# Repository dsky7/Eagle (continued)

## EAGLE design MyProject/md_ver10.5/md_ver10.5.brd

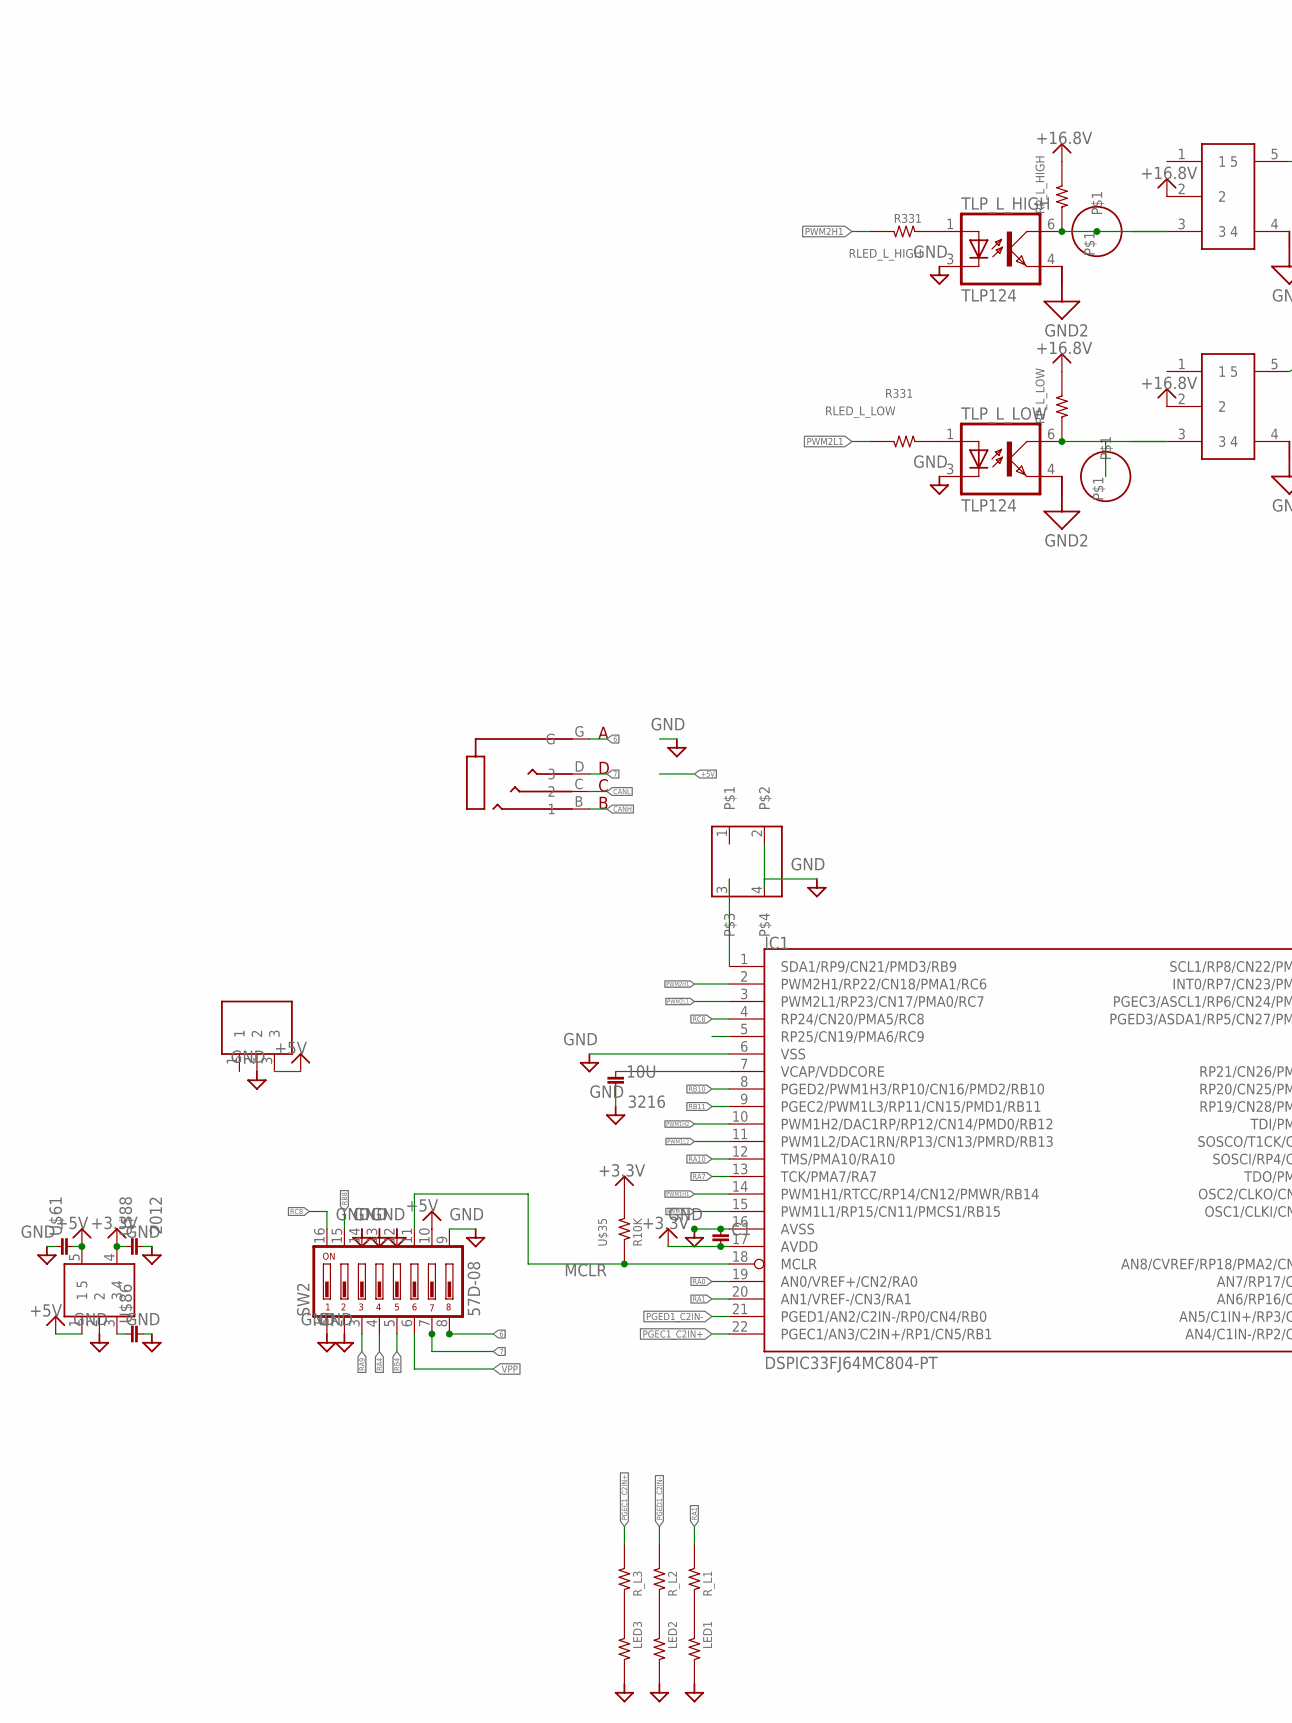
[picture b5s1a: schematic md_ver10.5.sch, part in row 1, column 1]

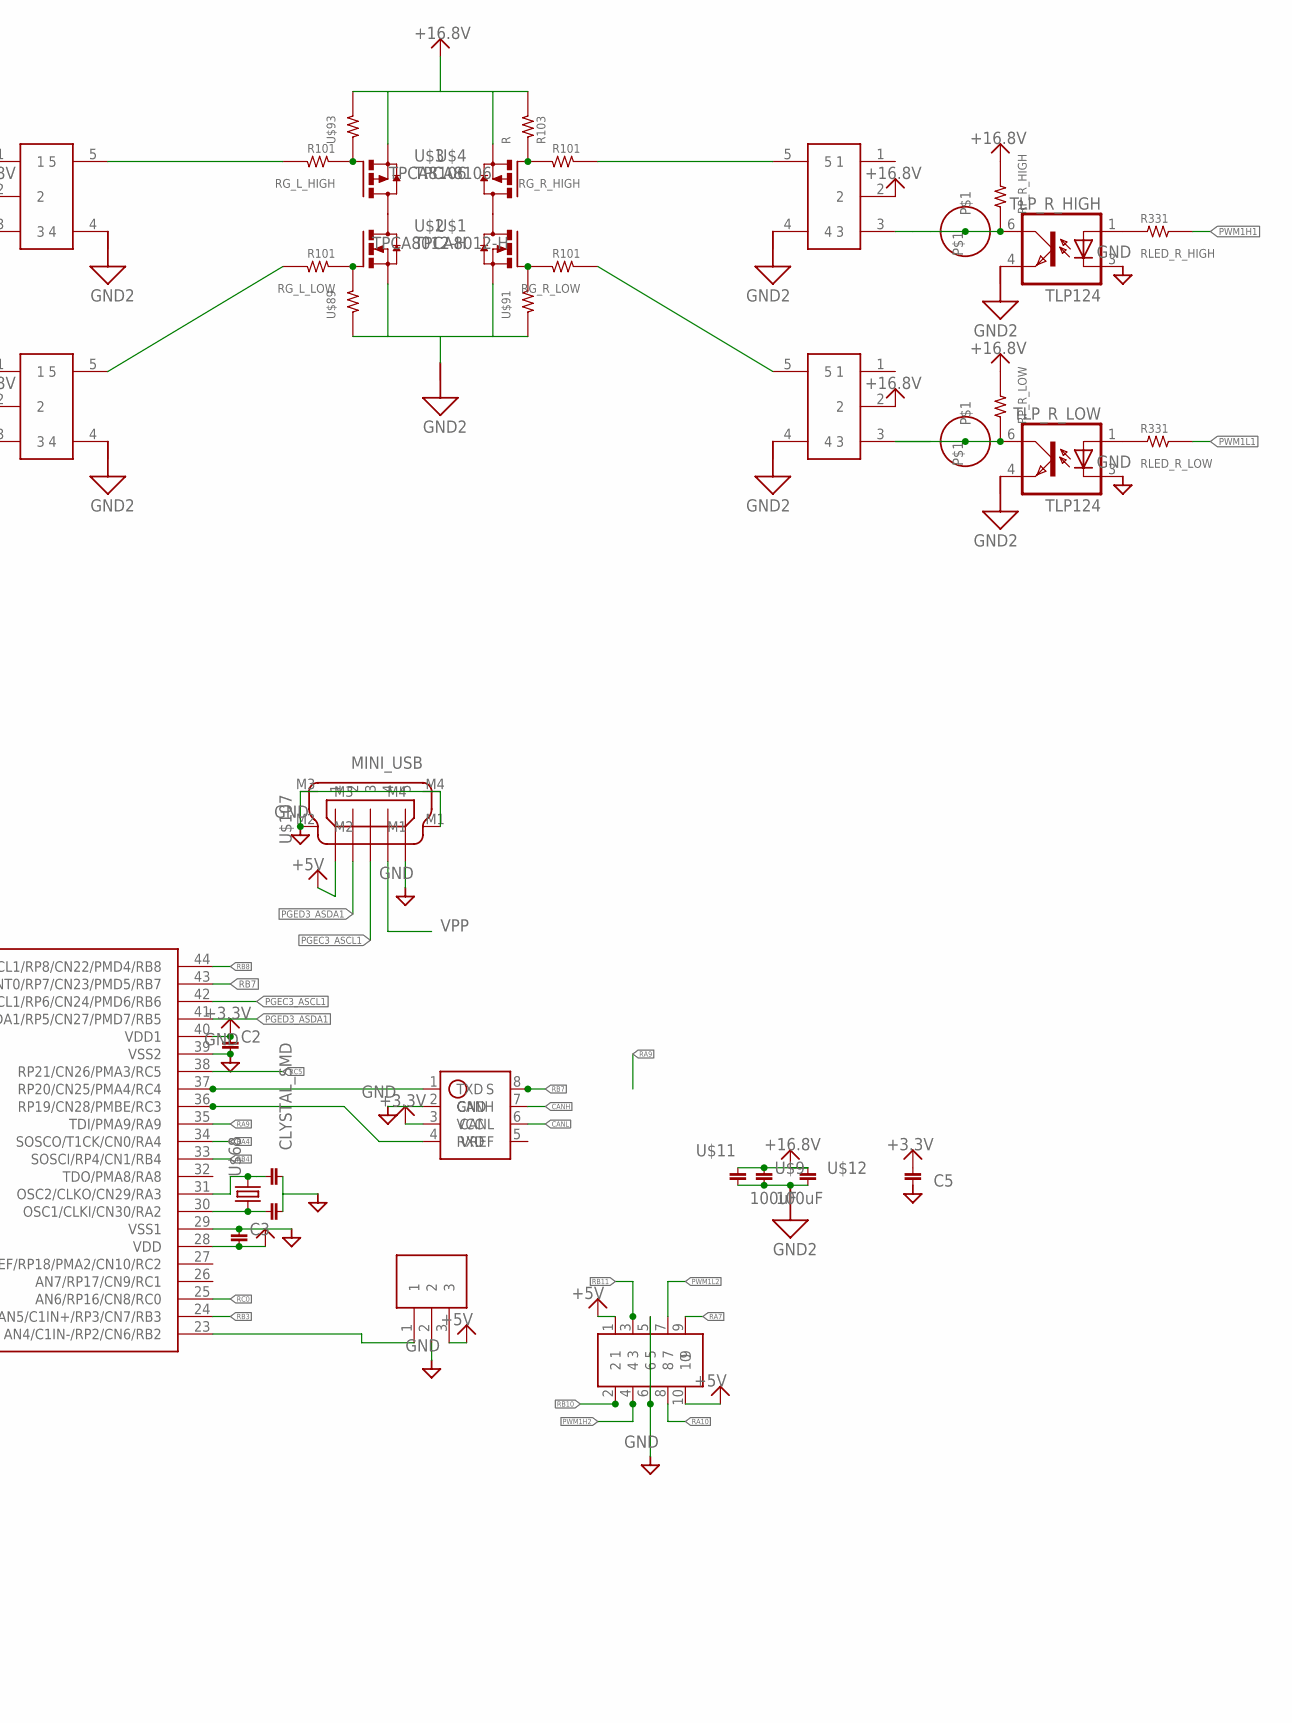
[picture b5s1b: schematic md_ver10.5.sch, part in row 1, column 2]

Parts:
10U: 3216
C: C5; 1608
C1, C2, C3: 1608
IC1: DSPIC33FJ64MC804-PT; TQFP44
IC2: TAR5SB; SSOP5-P-0.95
IC3: ＰＬ－ＩＲＭ
IC4: SN65HVD1050; SOIC8
IC5: Ｒ－７８Ｅ５．０
IC_L_HIGH: MCP1415; SOT23-5L
IC_L_LOW: MCP1415; SOT23-5L
IC_R_HIGH: MCP1415; SOT23-5L
IC_R_LOW: MCP1415; SOT23-5L
R: R103; 1608
RG_L_HIGH: R101; 1608
RG_L_LOW: R101; 1608
RG_R_HIGH: R101; 1608
RG_R_LOW: R101; 1608
RLED_L_HIGH: R331; 1608
RLED_L_LOW: R331; 1608
RLED_R_HIGH: R331; 1608
RLED_R_LOW: R331; 1608
RP_L_HIGH: RESISTOR__SMD; 1608
RP_L_LOW: RESISTOR__SMD; 1608
RP_R_HIGH: RESISTOR__SMD; 1608
RP_R_LOW: RESISTOR__SMD; 1608
SW1: TACT; TL1105
SW2: 57D-08; 57D
TLP_L_HIGH: TLP124; 11−4C1
TLP_L_LOW: TLP124; 11−4C1
TLP_R_HIGH: TLP124; 11−4C1
TLP_R_LOW: TLP124; 11−4C1
U$1, U$2: TPCA8012-H; 2-5Q1A
U$3, U$4: TPCA8106; 2-5Q1A
U$7, U$8: 20pF; 1608
U$9, U$11: 100uF; 3225
U$12: 3225
U$15: PIN_HEADER_52; PIN_HEADER_5*2
U$35: R10K; 1608
U$61, U$86: 1608
U$64: AUDIO4; AUDIO4_MJ
U$68: CLYSTAL_SMD; CRYSTAL_SMD
U$72: R_L3; 1608
U$74: LED3; 1608
U$75: R_L2; 1608
U$76: LED2; 1608
U$77: R_L1; 1608
U$78: LED1; 1608
U$88: 2012
U$89, U$91, U$93: RESISTOR__SMD; 1608
U$103, U$104, U$105, U$106: PAD1_4MM
U$107: MINI_USB

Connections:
6: SW2.8, U$64.G
7: SW2.7, U$64.D (3)
+3.3V: C.P$1 (1), C1.P$2 (2), C2.P$1 (1), C3.P$2 (2), IC1.17 (AVDD), IC1.28 (VDD), IC1.40 (VDD1), IC2.4, IC4.3 (VCC), U$35.2, U$88.1
+5V: IC2.1, IC2.5, IC3.3, IC5.3, SW2.10, U$15.1, U$15.10, U$61.P$2 (2), U$107.1
+16.8V: IC_L_HIGH.2, IC_L_LOW.2, IC_R_HIGH.2, IC_R_LOW.2, R.2, RP_L_HIGH.2, RP_L_LOW.2, RP_R_HIGH.2, RP_R_LOW.2, U$3.1 (S), U$3.2 (S), U$3.3 (S), U$4.1 (S), U$4.2 (S), U$4.3 (S), U$9.P$1 (1), U$11.P$1 (1), U$12.P$1 (1), U$93.2
CANH: IC4.7 (CANH), U$64.B (1)
CANL: IC4.6 (CANL), U$64.C (2)
GND: 10U.P$2 (2), C.P$2 (2), C1.P$1 (1), C2.P$2 (2), C3.P$1 (1), IC1.6 (VSS), IC1.16 (AVSS), IC1.29 (VSS1), IC1.39 (VSS2), IC2.2, IC3.2, IC4.2 (GND), IC5.2, SW1.2, SW1.4, SW2.1, SW2.2, SW2.9, SW2.12, SW2.13, SW2.14, TLP_L_HIGH.3 (C), TLP_L_LOW.3 (C), TLP_R_HIGH.3 (C), TLP_R_LOW.3 (C), U$7.P$2 (2), U$8.P$2 (2), U$15.5, U$15.6, U$61.P$1 (1), U$74.1, U$76.1, U$78.1, U$86.P$2 (2), U$88.2, U$107.5, U$107.M1, U$107.M2, U$107.M3, U$107.M4
GND2: IC_L_HIGH.4, IC_L_LOW.4, IC_R_HIGH.4, IC_R_LOW.4, TLP_L_HIGH.4 (EMIT), TLP_L_LOW.4 (EMIT), TLP_R_HIGH.4 (EMIT), TLP_R_LOW.4 (EMIT), U$1.1 (S), U$1.2 (S), U$1.3 (S), U$2.1 (S), U$2.2 (S), U$2.3 (S), U$9.P$2 (2), U$11.P$2 (2), U$12.P$2 (2), U$89.1, U$91.1
M1: U$2.5 (D), U$2.6 (D), U$2.7 (D), U$2.8 (D), U$3.5 (D), U$3.6 (D), U$3.7 (D), U$3.8 (D)
M2: U$1.5 (D), U$1.6 (D), U$1.7 (D), U$1.8 (D), U$4.5 (D), U$4.6 (D), U$4.7 (D), U$4.8 (D)
MCLR: IC1.18 (MCLR), SW2.11, U$35.1
unnamed: RG_L_LOW.1, U$2.4 (G), U$89.2
unnamed: IC2.3, U$86.P$1 (1)
unnamed: RLED_L_LOW.1, TLP_L_LOW.1 (A)
unnamed: RG_R_LOW.2, U$1.4 (G), U$91.2
unnamed: IC_L_HIGH.5, RG_L_HIGH.2
unnamed: IC_L_LOW.3, RP_L_LOW.1, TLP_L_LOW.6 (COL), U$104.P$1
unnamed: IC_R_LOW.5, RG_R_LOW.1
unnamed: RLED_R_LOW.1, TLP_R_LOW.1 (A)
unnamed: IC_L_HIGH.3, RP_L_HIGH.1, TLP_L_HIGH.6 (COL), U$103.P$1
unnamed: RLED_L_HIGH.1, TLP_L_HIGH.1 (A)
unnamed: IC_L_LOW.5, RG_L_LOW.2
unnamed: IC_R_HIGH.3, RP_R_HIGH.1, TLP_R_HIGH.6 (COL), U$105.P$1
unnamed: RLED_R_HIGH.1, TLP_R_HIGH.1 (A)
unnamed: IC1.23 (AN4/C1IN-/RP2/CN6/RB2), IC3.1
unnamed: IC_R_HIGH.5, RG_R_HIGH.1
unnamed: RG_L_HIGH.1, U$3.4 (G), U$93.1
unnamed: R.1, RG_R_HIGH.2, U$4.4 (G)
unnamed: U$72.1, U$74.2
unnamed: IC1.30 (OSC1/CLKI/CN30/RA2), U$7.P$1 (1), U$68.1
unnamed: IC1.31 (OSC2/CLKO/CN29/RA3), U$8.P$1 (1), U$68.2
unnamed: U$75.1, U$76.2
unnamed: U$77.1, U$78.2
unnamed: IC1.1 (SDA1/RP9/CN21/PMD3/RB9), SW1.3
unnamed: IC1.37 (RP20/CN25/PMA4/RC4), IC4.1 (TXD)
unnamed: IC1.36 (RP19/CN28/PMBE/RC3), IC4.4 (RXD)
PGEC1_C2IN+: IC1.22 (PGEC1/AN3/C2IN+/RP1/CN5/RB1), U$72.2
PGEC3_ASCL1: IC1.42 (PGEC3/ASCL1/RP6/CN24/PMD6/RB6), U$107.3
PGED1_C2IN-: IC1.21 (PGED1/AN2/C2IN-/RP0/CN4/RB0), U$75.2
PGED3_ASDA1: IC1.41 (PGED3/ASDA1/RP5/CN27/PMD7/RB5), U$107.2
PWM1H1: IC1.14 (PWM1H1/RTCC/RP14/CN12/PMWR/RB14), RLED_R_HIGH.2
PWM1H2: IC1.10 (PWM1H2/DAC1RP/RP12/CN14/PMD0/RB12), U$15.4
PWM1L1: IC1.15 (PWM1L1/RP15/CN11/PMCS1/RB15), RLED_R_LOW.2
PWM1L2: IC1.11 (PWM1L2/DAC1RN/RP13/CN13/PMRD/RB13), U$15.7
PWM2H1: IC1.2 (PWM2H1/RP22/CN18/PMA1/RC6), RLED_L_HIGH.2
PWM2L1: IC1.3 (PWM2L1/RP23/CN17/PMA0/RC7), RLED_L_LOW.2
RA0: IC1.19 (AN0/VREF+/CN2/RA0)
RA1: IC1.20 (AN1/VREF-/CN3/RA1), U$77.2
RA4: IC1.34 (SOSCO/T1CK/CN0/RA4), SW2.4
RA7: IC1.13 (TCK/PMA7/RA7), U$15.9
RA9: IC1.35 (TDI/PMA9/RA9), SW2.3
RA10: IC1.12 (TMS/PMA10/RA10), U$15.8
RB3: IC1.24 (AN5/C1IN+/RP3/CN7/RB3)
RB4: IC1.33 (SOSCI/RP4/CN1/RB4), SW2.5
RB7: IC1.43 (INT0/RP7/CN23/PMD5/RB7), IC4.8 (S)
RB8: IC1.44 (SCL1/RP8/CN22/PMD4/RB8), SW2.15
RB10: IC1.8 (PGED2/PWM1H3/RP10/CN16/PMD2/RB10), U$15.2
RB11: IC1.9 (PGEC2/PWM1L3/RP11/CN15/PMD1/RB11), U$15.3
RC0: IC1.25 (AN6/RP16/CN8/RC0)
RC5: IC1.38 (RP21/CN26/PMA3/RC5)
RC8: IC1.4 (RP24/CN20/PMA5/RC8), SW2.16
TLP_R_LOW: IC_R_LOW.3, RP_R_LOW.1, TLP_R_LOW.6 (COL), U$106.P$1
VCAP/VDDCORE: 10U.P$1 (1), IC1.7 (VCAP/VDDCORE)
VPP: SW2.6, U$107.4

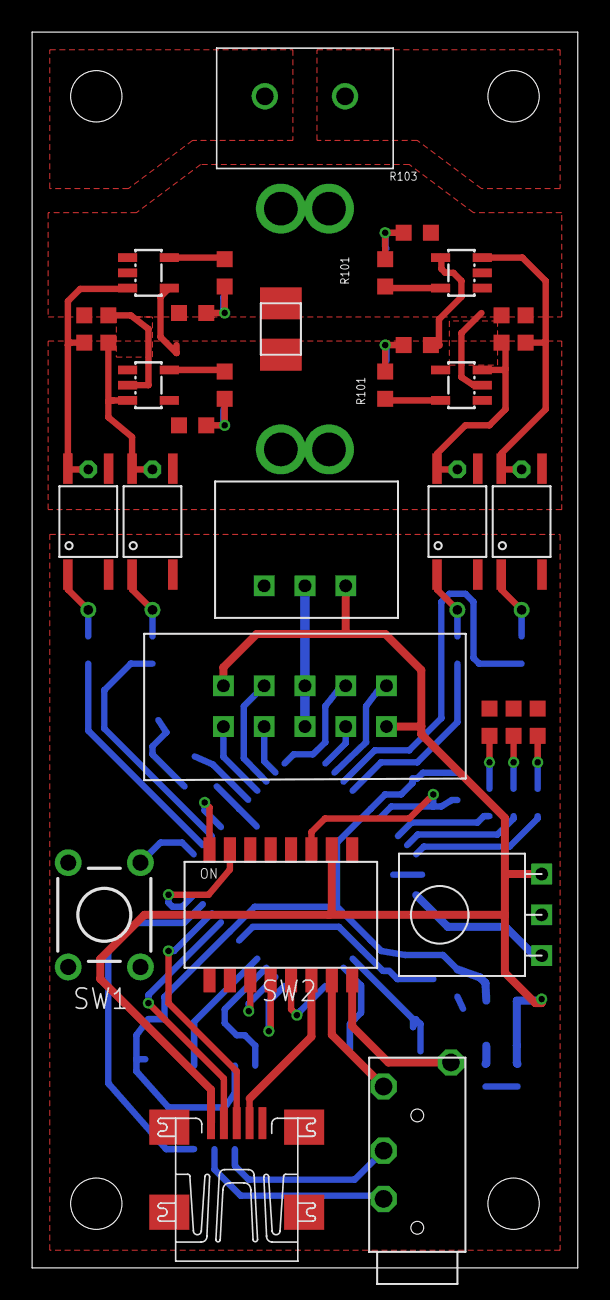
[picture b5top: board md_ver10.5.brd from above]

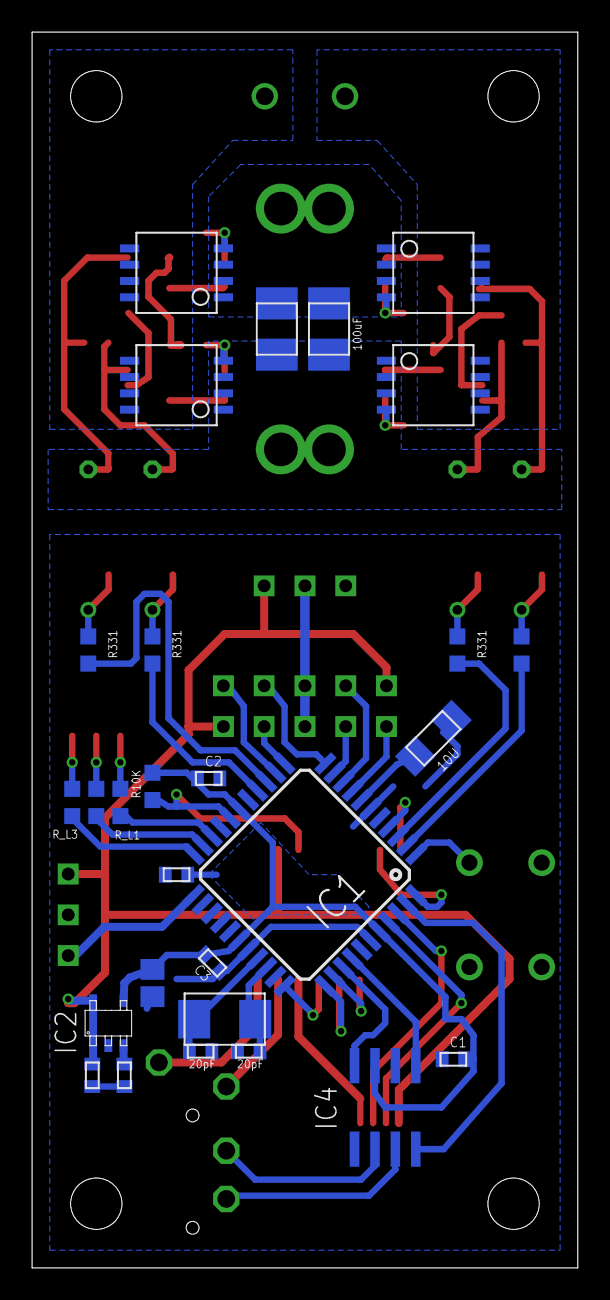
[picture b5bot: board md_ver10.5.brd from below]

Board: 2 copper layers, 34.0 x 77.0 mm, 63 parts (28 on the bottom side), 61 nets.

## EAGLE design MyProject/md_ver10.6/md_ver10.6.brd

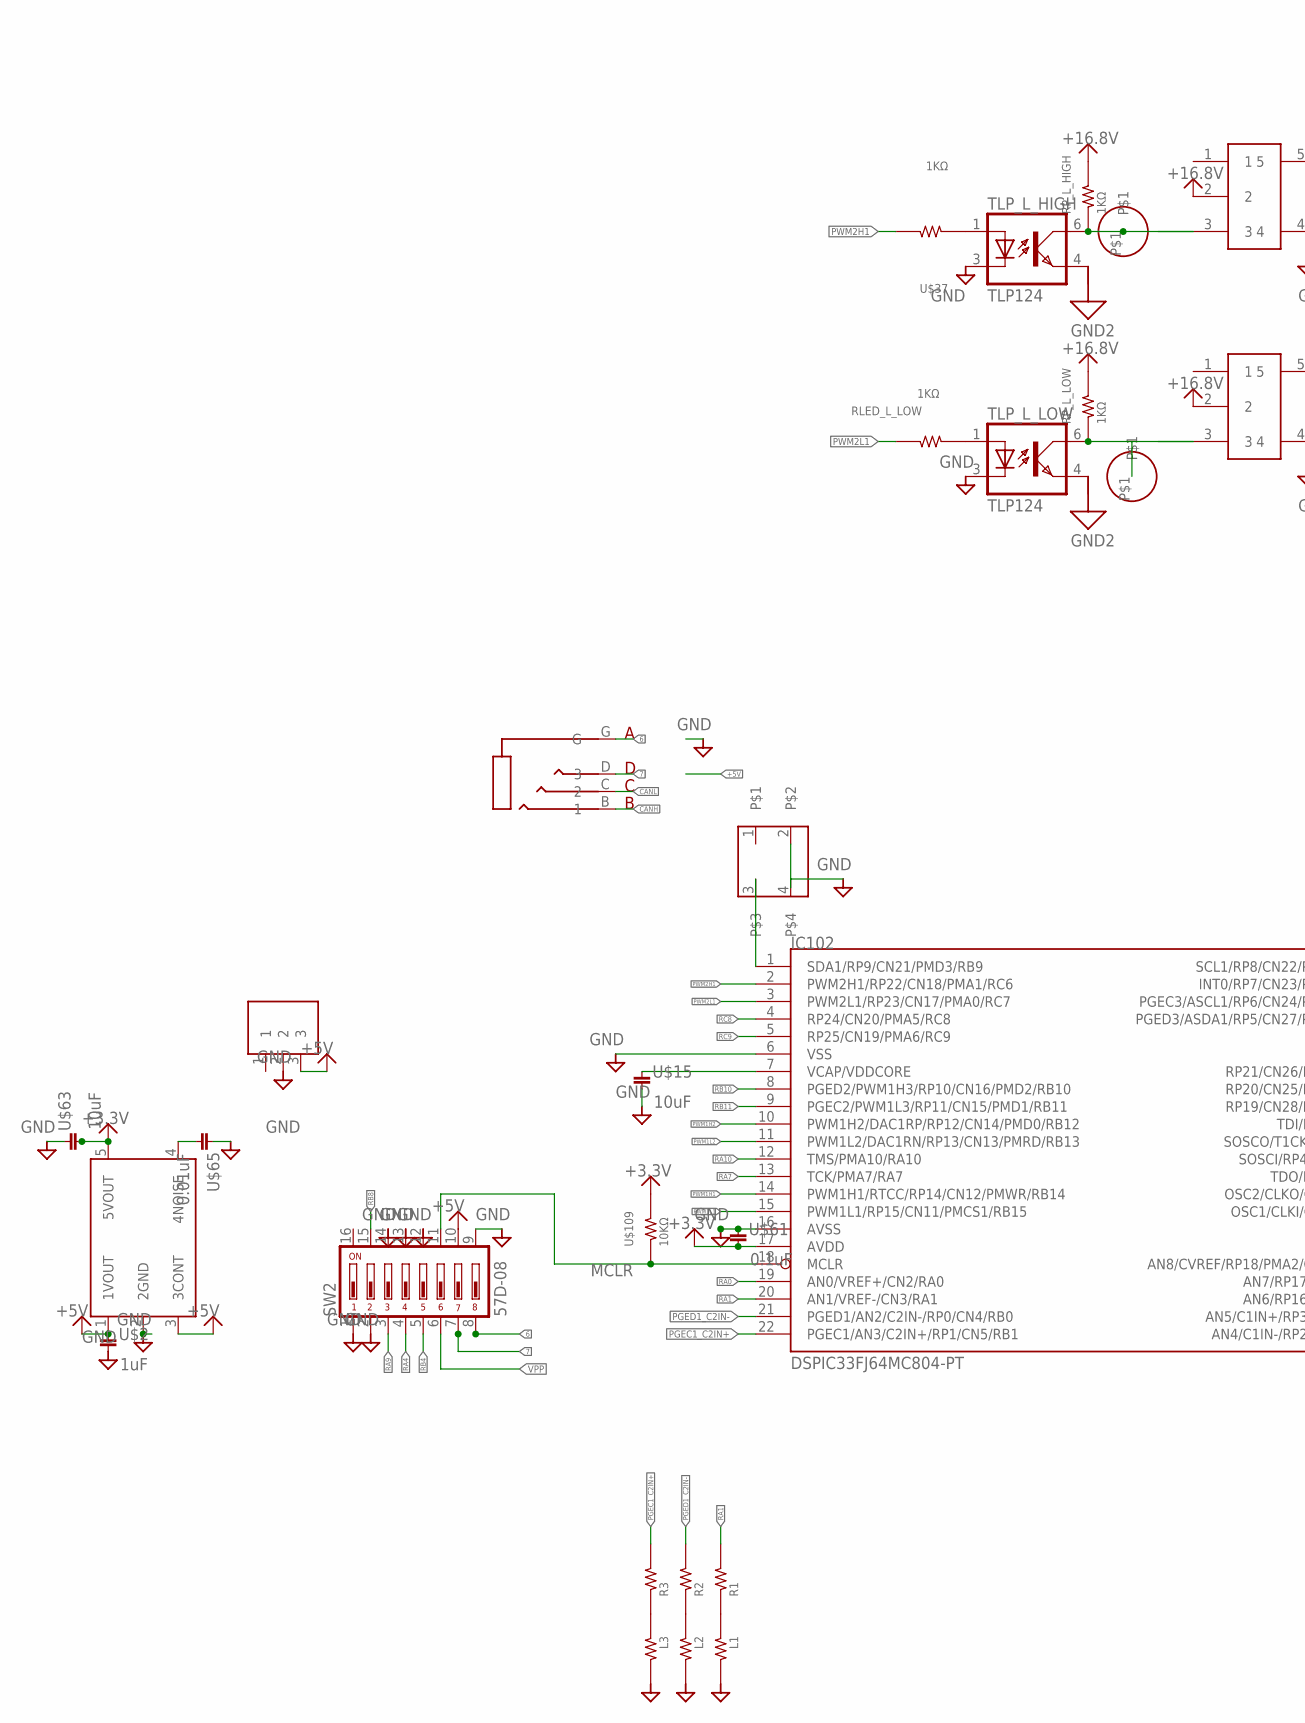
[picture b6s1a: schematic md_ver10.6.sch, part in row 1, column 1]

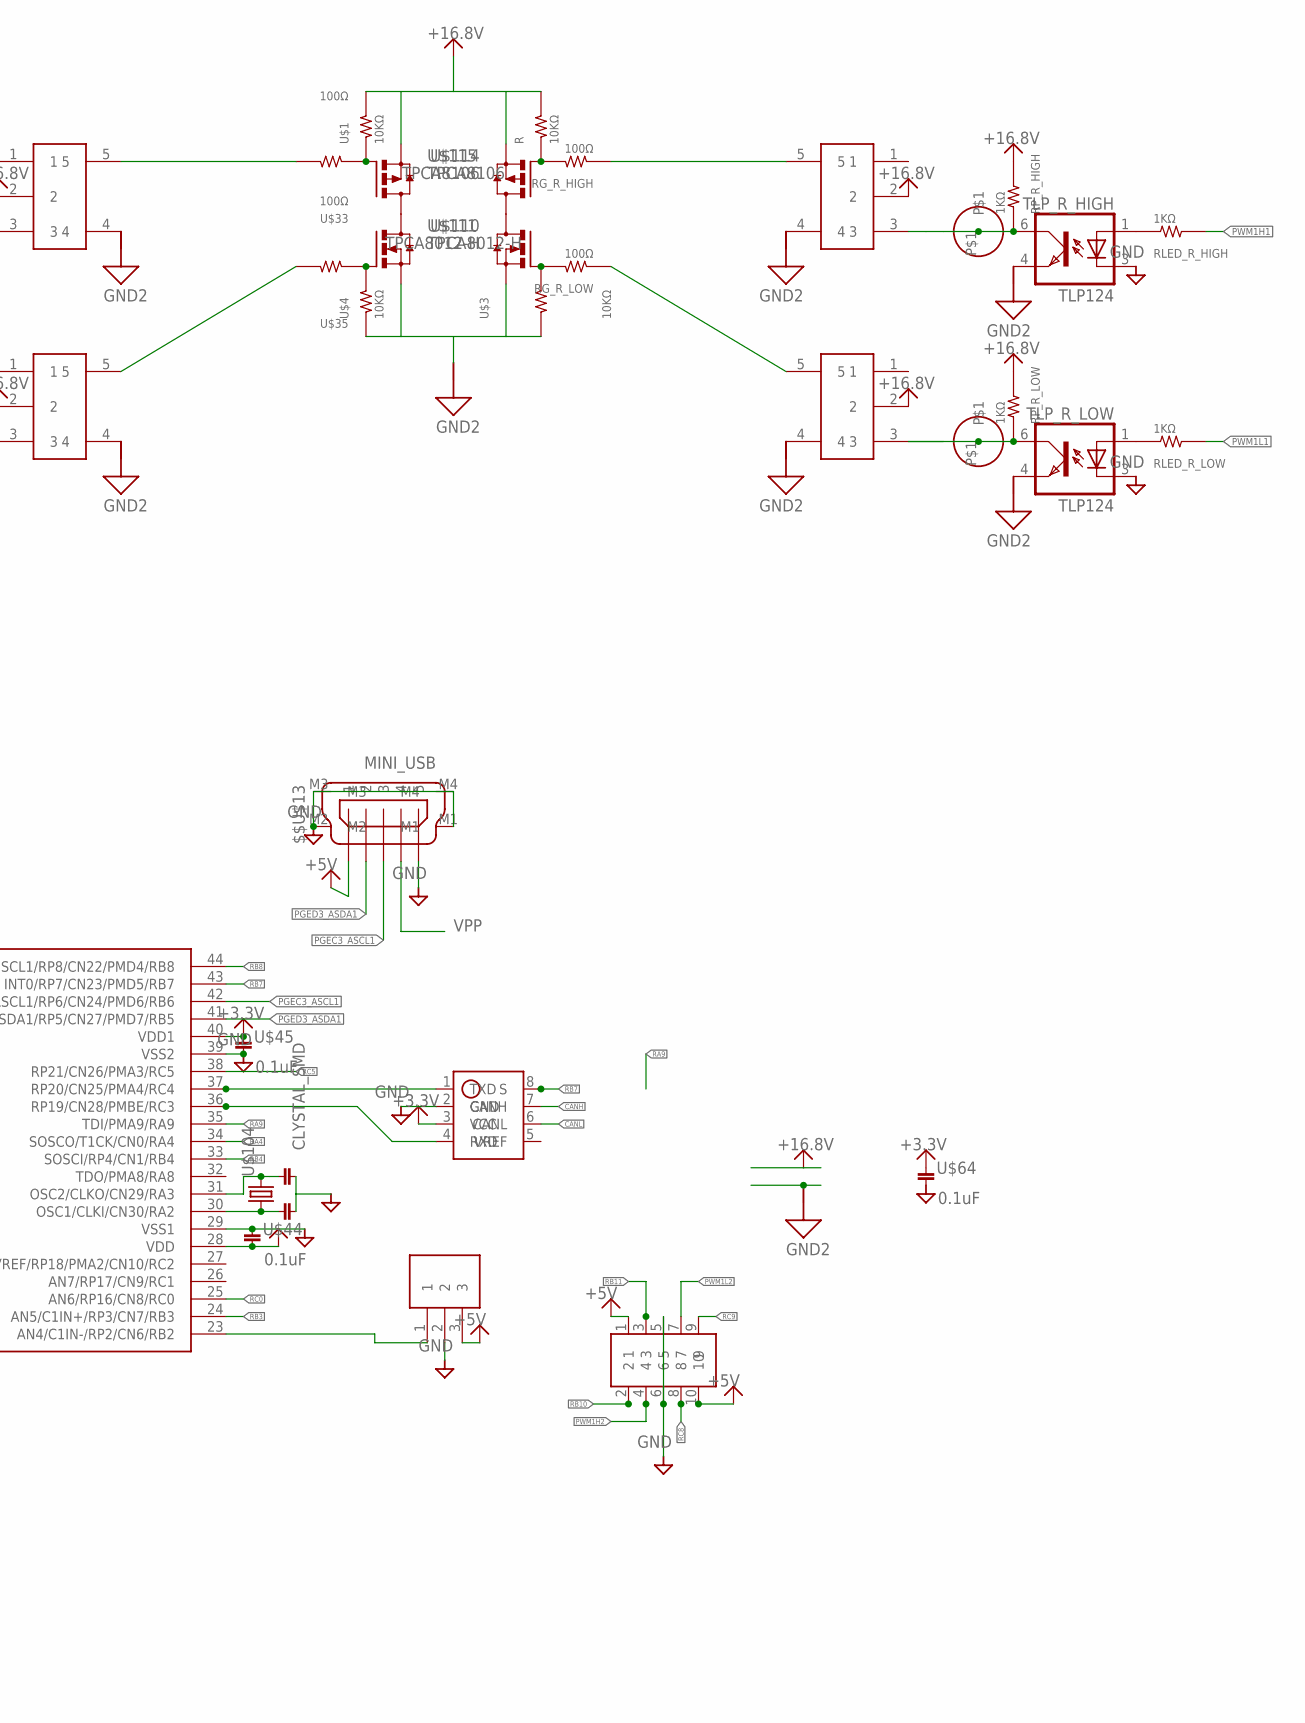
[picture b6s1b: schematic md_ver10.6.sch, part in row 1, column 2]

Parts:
$$U$5, $$U$6: PAD1_4MM
$$U$13: MINI_USB
$$U$14: AUDIO4; AUDIO4_MJ
$$U$102: 20pF; 1608
$$U$108: R1; 1608
IC1: Ｒ－７８Ｅ５．０
IC2: ＰＬ－ＩＲＭ
IC100: SN65HVD1050; SOIC8
IC101: TAR5SB; SSOP5-P-0.95
IC102: DSPIC33FJ64MC804-PT; TQFP44
IC_L_HIGH: MCP1415; SOT23-5L
IC_L_LOW: MCP1415; SOT23-5L
IC_R_HIGH: MCP1415; SOT23-5L
IC_R_LOW: MCP1415; SOT23-5L
R: 10KΩ; 1608
RG_R_HIGH: 100Ω; 1608
RG_R_LOW: 100Ω; 1608
RLED_L_LOW: 1KΩ; 1608
RLED_R_HIGH: 1KΩ; 1608
RLED_R_LOW: 1KΩ; 1608
RP_L_HIGH: 1KΩ; 1608
RP_L_LOW: 1KΩ; 1608
RP_R_HIGH: 1KΩ; 1608
RP_R_LOW: 1KΩ; 1608
SW1: TACT; TL1105
SW2: 57D-08; 57D
TLP_L_HIGH: TLP124; 11−4C1
TLP_L_LOW: TLP124; 11−4C1
TLP_R_HIGH: TLP124; 11−4C1
TLP_R_LOW: TLP124; 11−4C1
U$1, U$3, U$4, U$109: 10KΩ; 1608
U$2: 1uF; 1608
U$7, U$8: PAD1_4MM
U$9: PIN_HEADER_52; PIN_HEADER_5*2
U$10: L1; 1608
U$11: L2; 1608
U$12: L3; 1608
U$15, U$63: 10uF; 2012
U$33, U$35: 100Ω; 1608
U$37: 1KΩ; 1608
U$44, U$45, U$61, U$64: 0.1uF; 1608
U$65: 0.01uF; 1608
U$103: 20pF; 1608
U$104: CLYSTAL_SMD; CRYSTAL_SMD
U$106: R3; 1608
U$107: R2; 1608
U$110, U$111: TPCA8012-H; 2-5Q1A
U$114, U$115: TPCA8106; 2-5Q1A

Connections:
6: $$U$14.G, SW2.8
7: $$U$14.D (3), SW2.7
+3.3V: IC100.3 (VCC), IC101.5 (5VOUT), IC102.17 (AVDD), IC102.28 (VDD), IC102.40 (VDD1), U$44.P$2 (2), U$45.P$1 (1), U$61.P$2 (2), U$63.2, U$64.P$1 (1), U$109.2
+5V: $$U$13.1, IC1.3, IC2.3, IC101.1 (1VOUT), IC101.3 (3CONT), SW2.10, U$2.P$1 (1), U$9.1, U$9.10
+16.8V: IC_L_HIGH.2, IC_L_LOW.2, IC_R_HIGH.2, IC_R_LOW.2, R.2, RP_L_HIGH.2, RP_L_LOW.2, RP_R_HIGH.2, RP_R_LOW.2, U$1.2, U$114.1 (S), U$114.2 (S), U$114.3 (S), U$115.1 (S), U$115.2 (S), U$115.3 (S)
CANH: $$U$14.B (1), IC100.7 (CANH)
CANL: $$U$14.C (2), IC100.6 (CANL)
GND: $$U$13.5, $$U$13.M1, $$U$13.M2, $$U$13.M3, $$U$13.M4, $$U$102.P$2 (2), IC1.2, IC2.2, IC100.2 (GND), IC101.2 (2GND), IC102.6 (VSS), IC102.16 (AVSS), IC102.29 (VSS1), IC102.39 (VSS2), SW1.2, SW1.4, SW2.1, SW2.2, SW2.9, SW2.12, SW2.13, SW2.14, TLP_L_HIGH.3 (C), TLP_L_LOW.3 (C), TLP_R_HIGH.3 (C), TLP_R_LOW.3 (C), U$2.P$2 (2), U$9.5, U$9.6, U$10.1, U$11.1, U$12.1, U$15.2, U$44.P$1 (1), U$45.P$2 (2), U$61.P$1 (1), U$63.1, U$64.P$2 (2), U$65.P$1 (1), U$103.P$2 (2)
GND2: IC_L_HIGH.4, IC_L_LOW.4, IC_R_HIGH.4, IC_R_LOW.4, TLP_L_HIGH.4 (EMIT), TLP_L_LOW.4 (EMIT), TLP_R_HIGH.4 (EMIT), TLP_R_LOW.4 (EMIT), U$3.1, U$4.1, U$110.1 (S), U$110.2 (S), U$110.3 (S), U$111.1 (S), U$111.2 (S), U$111.3 (S)
M1: U$111.5 (D), U$111.6 (D), U$111.7 (D), U$111.8 (D), U$115.5 (D), U$115.6 (D), U$115.7 (D), U$115.8 (D)
M2: U$110.5 (D), U$110.6 (D), U$110.7 (D), U$110.8 (D), U$114.5 (D), U$114.6 (D), U$114.7 (D), U$114.8 (D)
MCLR: IC102.18 (MCLR), SW2.11, U$109.1
unnamed: U$4.2, U$35.1, U$111.4 (G)
unnamed: IC101.4 (4NOISE), U$65.P$2 (2)
unnamed: RLED_L_LOW.1, TLP_L_LOW.1 (A)
unnamed: RG_R_LOW.2, U$3.2, U$110.4 (G)
unnamed: IC_L_HIGH.5, U$33.2
unnamed: $$U$6.P$1, IC_L_LOW.3, RP_L_LOW.1, TLP_L_LOW.6 (COL)
unnamed: IC_R_LOW.5, RG_R_LOW.1
unnamed: RLED_R_LOW.1, TLP_R_LOW.1 (A)
unnamed: TLP_L_HIGH.1 (A), U$37.1
unnamed: $$U$5.P$1, IC_L_HIGH.3, RP_L_HIGH.1, TLP_L_HIGH.6 (COL)
unnamed: IC_L_LOW.5, U$35.2
unnamed: IC_R_HIGH.3, RP_R_HIGH.1, TLP_R_HIGH.6 (COL), U$8.P$1
unnamed: RLED_R_HIGH.1, TLP_R_HIGH.1 (A)
unnamed: IC2.1, IC102.23 (AN4/C1IN-/RP2/CN6/RB2)
unnamed: IC_R_HIGH.5, RG_R_HIGH.1
unnamed: U$1.1, U$33.1, U$115.4 (G)
unnamed: R.1, RG_R_HIGH.2, U$114.4 (G)
unnamed: U$12.2, U$106.1
unnamed: $$U$102.P$1 (1), IC102.30 (OSC1/CLKI/CN30/RA2), U$104.1
unnamed: IC102.31 (OSC2/CLKO/CN29/RA3), U$103.P$1 (1), U$104.2
unnamed: U$11.2, U$107.1
unnamed: $$U$108.1, U$10.2
unnamed: IC102.1 (SDA1/RP9/CN21/PMD3/RB9), SW1.3
unnamed: IC100.1 (TXD), IC102.37 (RP20/CN25/PMA4/RC4)
unnamed: IC100.4 (RXD), IC102.36 (RP19/CN28/PMBE/RC3)
PGEC1_C2IN+: IC102.22 (PGEC1/AN3/C2IN+/RP1/CN5/RB1), U$106.2
PGEC3_ASCL1: $$U$13.3, IC102.42 (PGEC3/ASCL1/RP6/CN24/PMD6/RB6)
PGED1_C2IN-: IC102.21 (PGED1/AN2/C2IN-/RP0/CN4/RB0), U$107.2
PGED3_ASDA1: $$U$13.2, IC102.41 (PGED3/ASDA1/RP5/CN27/PMD7/RB5)
PWM1H1: IC102.14 (PWM1H1/RTCC/RP14/CN12/PMWR/RB14), RLED_R_HIGH.2
PWM1H2: IC102.10 (PWM1H2/DAC1RP/RP12/CN14/PMD0/RB12), U$9.4
PWM1L1: IC102.15 (PWM1L1/RP15/CN11/PMCS1/RB15), RLED_R_LOW.2
PWM1L2: IC102.11 (PWM1L2/DAC1RN/RP13/CN13/PMRD/RB13), U$9.7
PWM2H1: IC102.2 (PWM2H1/RP22/CN18/PMA1/RC6), U$37.2
PWM2L1: IC102.3 (PWM2L1/RP23/CN17/PMA0/RC7), RLED_L_LOW.2
RA0: IC102.19 (AN0/VREF+/CN2/RA0)
RA1: $$U$108.2, IC102.20 (AN1/VREF-/CN3/RA1)
RA4: IC102.34 (SOSCO/T1CK/CN0/RA4), SW2.4
RA7: IC102.13 (TCK/PMA7/RA7)
RA9: IC102.35 (TDI/PMA9/RA9), SW2.3
RA10: IC102.12 (TMS/PMA10/RA10)
RB3: IC102.24 (AN5/C1IN+/RP3/CN7/RB3)
RB4: IC102.33 (SOSCI/RP4/CN1/RB4), SW2.5
RB7: IC100.8 (S), IC102.43 (INT0/RP7/CN23/PMD5/RB7)
RB8: IC102.44 (SCL1/RP8/CN22/PMD4/RB8), SW2.15
RB10: IC102.8 (PGED2/PWM1H3/RP10/CN16/PMD2/RB10), U$9.2
RB11: IC102.9 (PGEC2/PWM1L3/RP11/CN15/PMD1/RB11), U$9.3
RC0: IC102.25 (AN6/RP16/CN8/RC0)
RC5: IC102.38 (RP21/CN26/PMA3/RC5)
RC8: IC102.4 (RP24/CN20/PMA5/RC8), U$9.8
RC9: IC102.5 (RP25/CN19/PMA6/RC9), U$9.9
TLP_R_LOW: IC_R_LOW.3, RP_R_LOW.1, TLP_R_LOW.6 (COL), U$7.P$1
VCAP/VDDCORE: IC102.7 (VCAP/VDDCORE), U$15.1
VPP: $$U$13.4, SW2.6

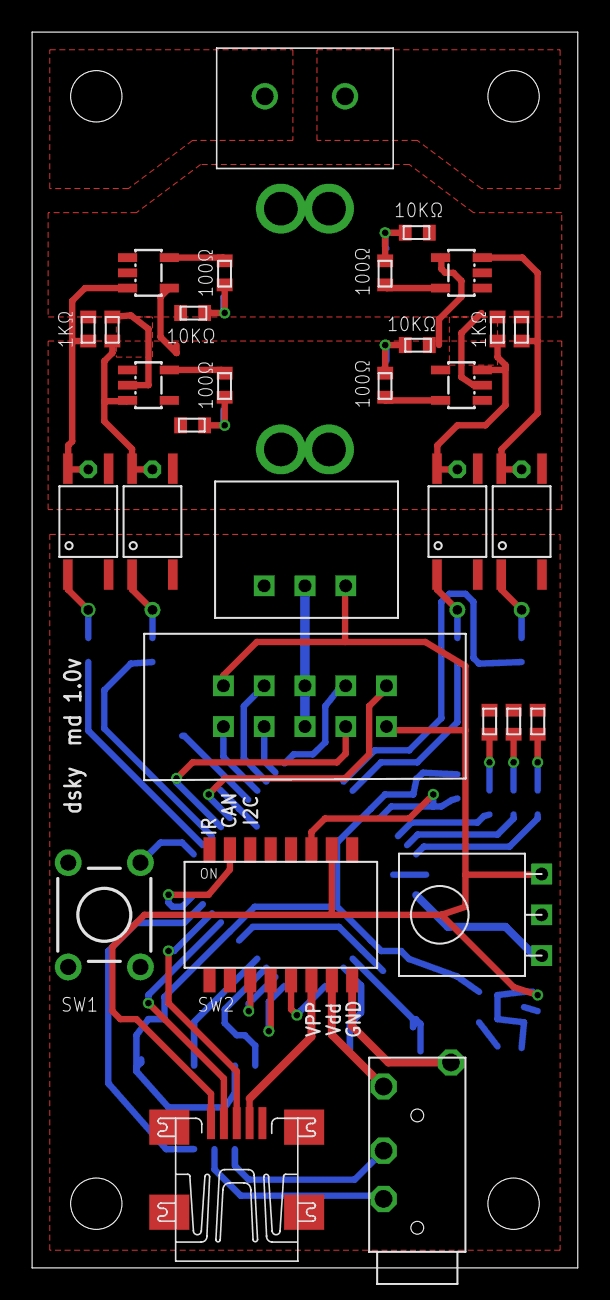
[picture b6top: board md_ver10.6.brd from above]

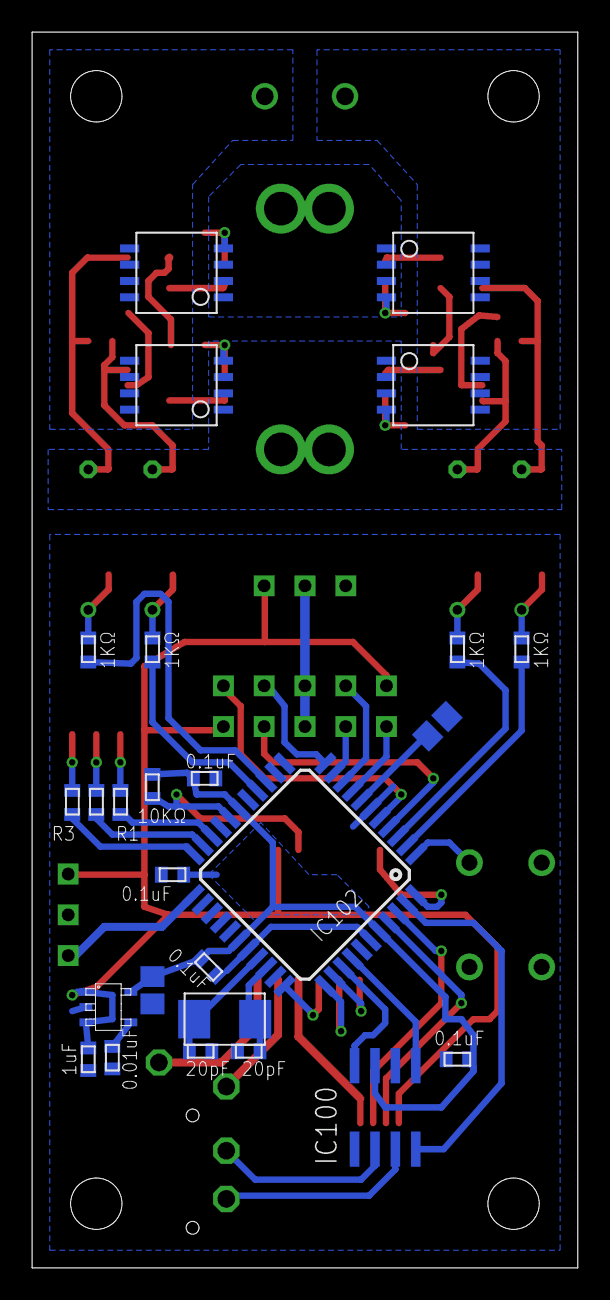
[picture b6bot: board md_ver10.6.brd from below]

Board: 2 copper layers, 34.0 x 77.0 mm, 60 parts (26 on the bottom side), 60 nets.
